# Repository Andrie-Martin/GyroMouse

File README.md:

# 🖱️ GyroMouse  
**A Bluetooth Low Energy (BLE) Air Mouse built with ESP32 and MPU6050**

GyroMouse is a custom-built **air mouse** that allows users to control a computer cursor and scrolling actions using **hand movements in mid-air**. Instead of relying on an optical sensor and a flat surface, this project uses an **inertial measurement unit (IMU)** and Bluetooth Low Energy to explore surface-free human–computer interaction.

This repository documents **how the project was designed, built, tested, and refined**, from the initial idea to a fully working prototype.

## 📖 Project Background

The idea behind GyroMouse started with a simple problem: traditional mice require a physical surface, which limits their use during presentations, smart TV navigation, and mobile setups. We wanted to create an input device that could work **anywhere**, relying only on hand motion.

After evaluating different approaches—wired, wireless, and gesture-based—we decided to design an **air mouse** that uses gyroscopic motion and Bluetooth connectivity while remaining compact and portable.

## 🧠 System Overview

GyroMouse consists of four main subsystems:

- **ESP32 microcontroller** – operates as a Bluetooth Low Energy Human Interface Device (HID)
- **MPU6050 IMU** – provides gyroscope and accelerometer data
- **Physical buttons** – left click, right click, and scroll-lock
- **Battery-powered system** – enables fully wireless operation

The ESP32 continuously reads motion data from the MPU6050 and translates it into mouse actions sent wirelessly to a computer.

## 🔄 Project Roadmap

Before any hardware was built, the entire workflow of the project was planned.

### Overall Development Flow

The project followed these stages:
1. Idea evaluation and feature brainstorming  
2. Hardware component selection  
3. Initial breadboard testing  
4. Firmware development  
5. PCB layout and fabrication  
6. Final assembly and testing  

## ⚙️ Software and Progress Logic Flow

To define how the system behaves during operation, a detailed software and its implementation to the hardware (progress) flowchart was created.

### Software Flowchart

The logic follows this sequence:
- Initialize serial communication  
- Initialize BLE mouse service  
- Check MPU6050 connection  
- Configure sensor settings and button pins  
- Wait for BLE connection  
- Continuously:
  - read gyroscope data  
  - apply deadzone filtering  
  - move cursor or scroll  
  - handle button presses  

## 🧪 Breadboard Testing
All components were first tested on a breadboard before transitioning to a permanent PCB to minimize errors.
Initial testing was performed using a breadboard to verify:
- Bluetooth connectivity  
- Gyroscope responsiveness  
- Cursor movement accuracy  
- Button functionality  

This step helped identify and resolve issues early in the development process.

## 🧱 PCB Fabrication Process

PCB fabrication involved several manual steps:
1. Drawing the PCB layout  
2. Etching using ferric chloride  
3. Cleaning the board  
4. Drilling component holes  
5. Soldering components  

Manual PCB layout drawing was chosen after automated transfer methods produced inconsistent and unclear traces.

## ⚠️ Challenges Encountered

| Challenge | Solution |
|---------|----------|
| ESP32 not detected | Installed the correct ESP32 board package |
| MPU6050 issues | Used a compatible and stable sensor library |
| PCB transfer failed | Switched to manual PCB etching |
| Upload errors | Used ESP32 boot mode during flashing |
| Drilling precision | Used PCB-specific drill bits |

## ✅ Final Output

The completed **GyroMouse** functions as a fully wireless **Bluetooth Low Energy air mouse**, capable of smooth cursor control and scrolling **without requiring a physical surface**.  
The device demonstrates stable BLE connectivity, responsive motion tracking, and reliable button input.

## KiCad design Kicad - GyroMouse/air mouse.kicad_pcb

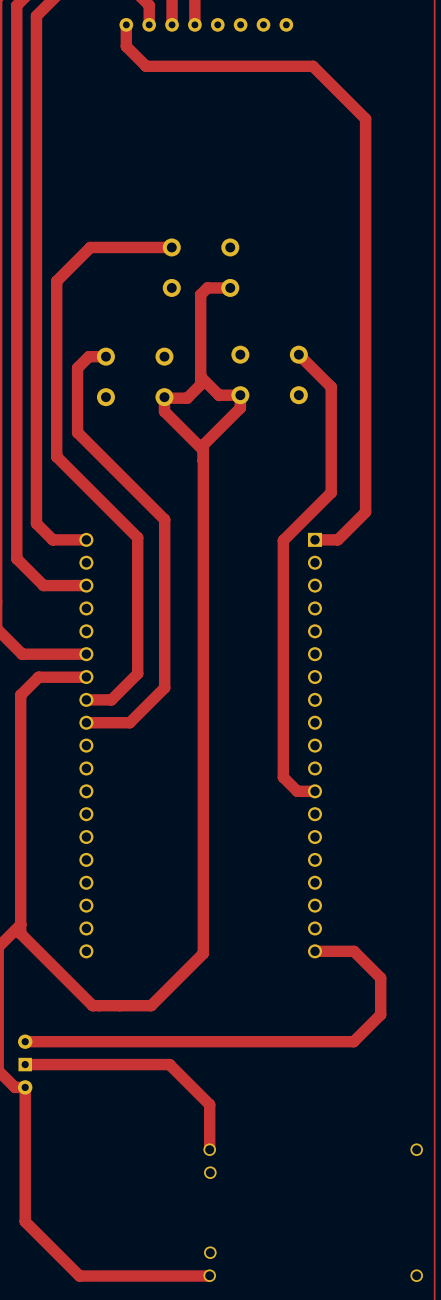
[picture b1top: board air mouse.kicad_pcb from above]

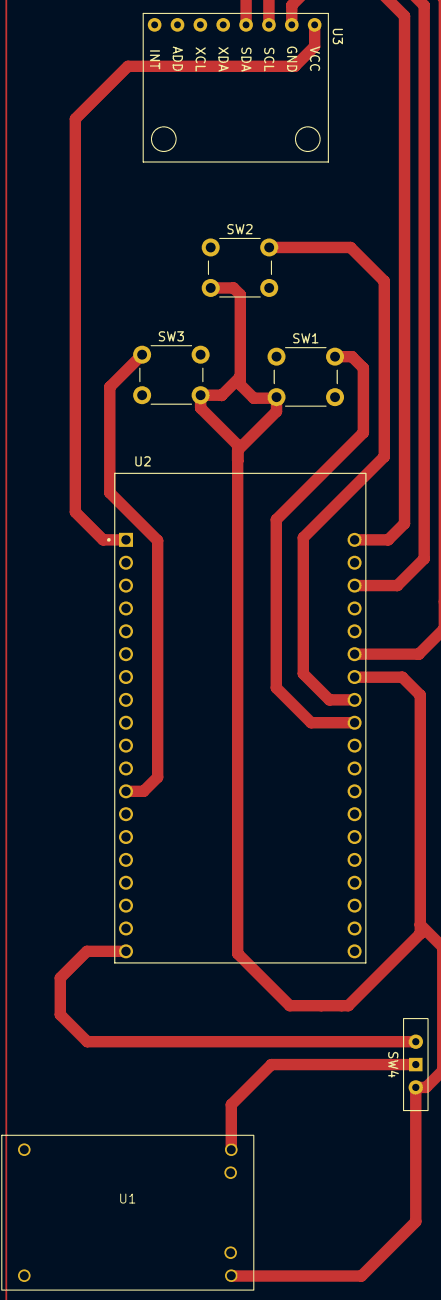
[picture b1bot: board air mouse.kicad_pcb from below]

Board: 2 copper layers, 7 parts (7 on the bottom side), 10 nets.

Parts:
SW1: SW_Left; SW_PUSH_6mm
SW2: SW_Scroll; SW_PUSH_6mm
SW3: SW_Right; SW_PUSH_6mm
SW4: SW_SPDT; SW_Slide-03_Wuerth-WS-SLTV_10x2.5x6.4_P2.54mm
U1: TP4056 Li-Ion Charger; TP4056 Customized
U2: ESP32-DEVKITC-32D; MODULE_ESP32-DEVKITC-32D
U3: module_mpu6050

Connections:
GND: SW1.2, SW2.2, SW3.2, SW4.2 (A), U1.4 (OUT-), U2.J3-7 (GND2)
INPUT: U2.J2-1 (3V3), U3.1 (VCC)
unnamed: SW4.1 (B), U1.3 (OUT+)
unnamed: SW4.3 (C), U2.J2-19 (EXT_5V)
unnamed: U2.J3-1 (GND3), U3.2 (GND)
unnamed: SW3.1, U2.J2-12 (IO14)
unnamed: SW1.1, U2.J3-9 (IO18)
unnamed: SW2.1, U2.J3-8 (IO19)
unnamed: U2.J3-6 (IO21), U3.4 (SDA)
unnamed: U2.J3-3 (IO22), U3.3 (SCL)
